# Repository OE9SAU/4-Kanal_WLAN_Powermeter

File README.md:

# 4-Channel WiFi Power Meter Using Wemos D1 and INA226 (or Compatible INAxxx Sensors)

This project utilizes the Wemos D1 (ESP8266) microcontroller paired with INA226 current/voltage sensors (or any compatible INAxxx series) to provide precise, real-time measurements of electrical parameters across four independent channels.

Technical Specifications:
* Voltage Measurement Range: up to 36 V DC per channel
* Current Measurement Range: up to 13-15A per channel (when PCB traces are properly soldered (~0,3 mm) around 20A
* Sensor: INA226 (bidirectional current and voltage sensor with high accuracy)
* Microcontroller: Wemos D1 (ESP8266) for WiFi connectivity and data transmission
* Communication: Wireless data streaming via WiFi for remote dasboard monitoring and MQTT broker
* Applications: Multi-channel power consumption monitoring, load analysis, and energy management

| Parameter              | Wert                                              |
| ---------------------- | ------------------------------------------------- |
| Shunt-Widerstand       | 2 mΩ                                              |
| Maximalstrom           | 20 A                                              |
| Shuntspannung @ 20 A   | 40 mV                                             |
| Verlustleistung @ 20 A | 0.8 W                                             |
| Current\_LSB           | 625 µA                                            |
| Calibration-Wert       | **4096**                                          |
| Stromauflösung         | 0.625 mA / Bit                                    |
| Leistungsauflösung     | $25 \cdot \text{LSB} = \boxed{15.625\,\text{mW}}$ |

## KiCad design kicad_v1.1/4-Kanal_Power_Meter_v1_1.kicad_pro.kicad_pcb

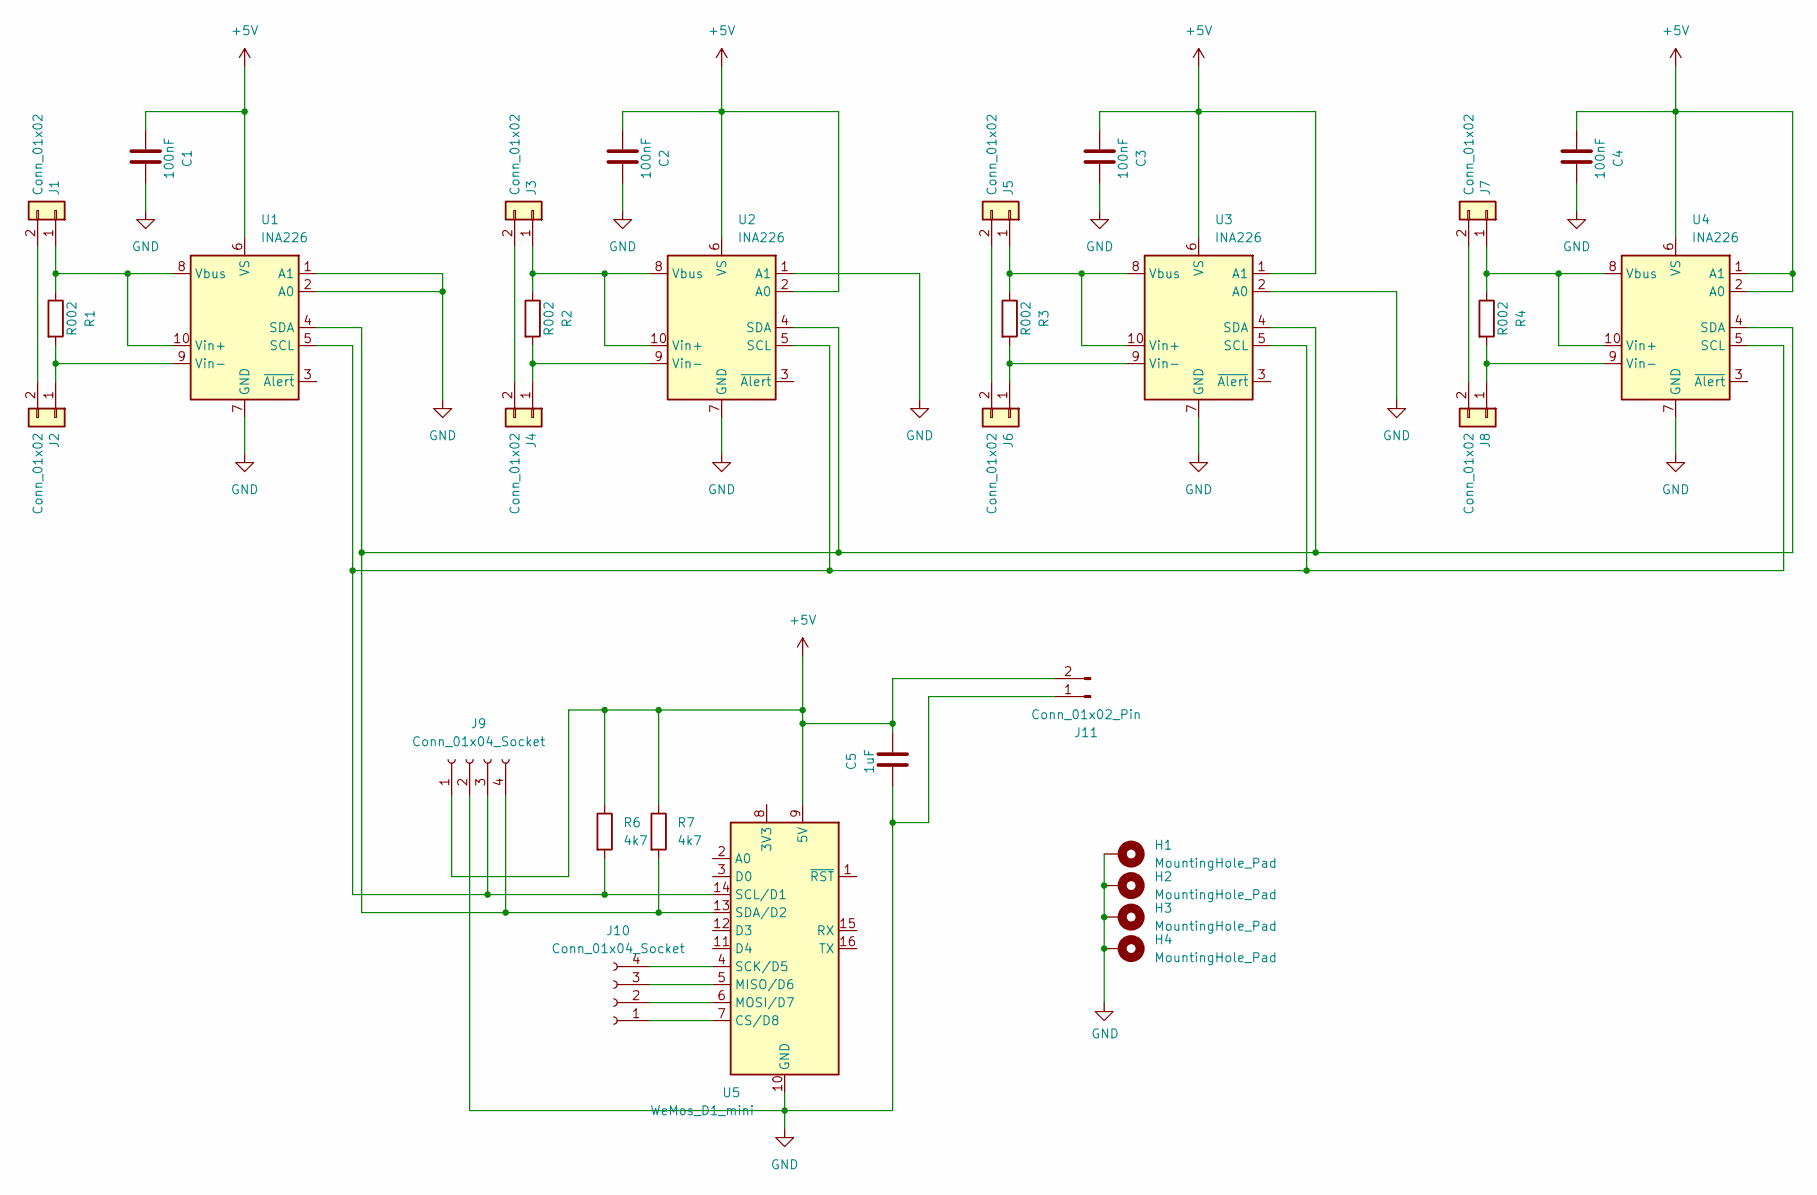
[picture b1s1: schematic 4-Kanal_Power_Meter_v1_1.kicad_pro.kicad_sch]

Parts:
C1, C2, C3, C4: 100nF; C_0805_2012Metric_Pad1.18x1.45mm_HandSolder
C5: 1uF; C_0805_2012Metric_Pad1.18x1.45mm_HandSolder
H1, H2, H3, H4: MountingHole_Pad; MountingHole_3.5mm_Pad
J1, J2, J3, J4, J5, J6, J7, J8: Conn_01x02; PowerPole_PP45_1336G1_1x2_Horizontal; MPN 1336G1
J9, J10: Conn_01x04_Socket; PinSocket_1x04_P2.54mm_Vertical
J11: Conn_01x02_Pin; PinHeader_1x02_P2.54mm_Horizontal
R1, R2, R3, R4: R002; R_2512_6332Metric_Pad1.40x3.35mm_HandSolder
R6, R7: 4k7; R_0805_2012Metric_Pad1.20x1.40mm_HandSolder
U1, U2, U3, U4: INA226; VSSOP-10_3x3mm_P0.5mm
U5: WeMos_D1_mini; WEMOS_D1_mini_light

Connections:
GND: C1.2, C2.2, C3.2, C4.2, C5.2, H1.1, H2.1, H3.1, H4.1, J9.2, J11.1, U1.1 (A1), U1.2 (A0), U1.7 (GND), U2.1 (A1), U2.7 (GND), U3.2 (A0), U3.7 (GND), U4.7 (GND), U5.10 (GND)
unnamed: J1.1, R1.1, U1.8 (Vbus), U1.10 (Vin+)
unnamed: J1.2, J2.2
unnamed: J2.1, R1.2, U1.9 (Vin-)
unnamed: J3.1, R2.1, U2.8 (Vbus), U2.10 (Vin+)
unnamed: J3.2, J4.2
unnamed: J4.1, R2.2, U2.9 (Vin-)
unnamed: J5.1, R3.1, U3.8 (Vbus), U3.10 (Vin+)
unnamed: J5.2, J6.2
unnamed: J6.1, R3.2, U3.9 (Vin-)
unnamed: J7.1, R4.1, U4.8 (Vbus), U4.10 (Vin+)
unnamed: J7.2, J8.2
unnamed: J8.1, R4.2, U4.9 (Vin-)
unnamed: J9.3, R6.2, U1.5 (SCL), U2.5 (SCL), U3.5 (SCL), U4.5 (SCL), U5.14 (SCL/D1)
unnamed: J9.4, R7.2, U1.4 (SDA), U2.4 (SDA), U3.4 (SDA), U4.4 (SDA), U5.13 (SDA/D2)
unnamed: J10.1, U5.7 (CS/D8)
unnamed: J10.2, U5.6 (MOSI/D7)
unnamed: J10.3, U5.5 (MISO/D6)
unnamed: J10.4, U5.4 (SCK/D5)

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
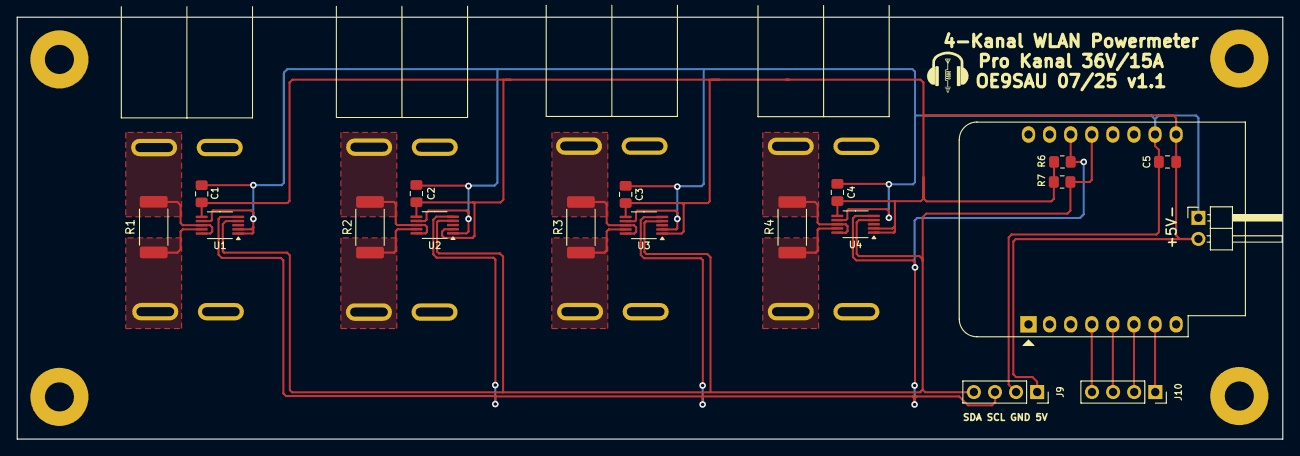
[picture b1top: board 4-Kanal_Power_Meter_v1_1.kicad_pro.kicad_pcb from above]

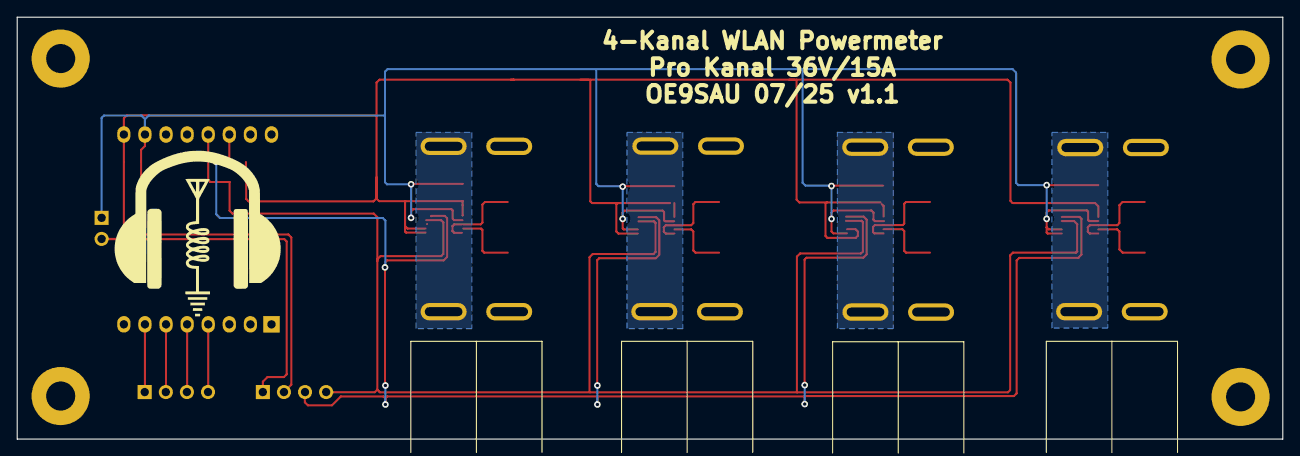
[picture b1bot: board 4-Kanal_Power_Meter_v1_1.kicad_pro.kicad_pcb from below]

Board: 2 copper layers, 152.4 x 50.8 mm, 33 parts (5 on the bottom side), 21 nets.

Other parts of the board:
G0, G1: LOGO

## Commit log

2025-06-11 PCB Update
2025-06-13 Update Files
2025-06-13 png update
2025-06-16 Upload Code
2025-06-30 Update Code
2025-07-01 Add housing
2025-07-01 Code updaze
2025-07-02 pics
2025-07-02 Update pics
2025-07-02 Pic Update
2025-07-02 housing
2025-07-03 Commits
2025-07-03 v1.1
2025-07-04 Lib + uC update
2025-07-04 file update
2025-07-06 html update
2025-07-14 Update housing
2025-07-20 Housing_v2_v3
2025-07-23 update uC
2025-07-24 v4.1_mDNS
2025-07-24 v4.1
2025-08-02 file upd
2025-08-14 code update
